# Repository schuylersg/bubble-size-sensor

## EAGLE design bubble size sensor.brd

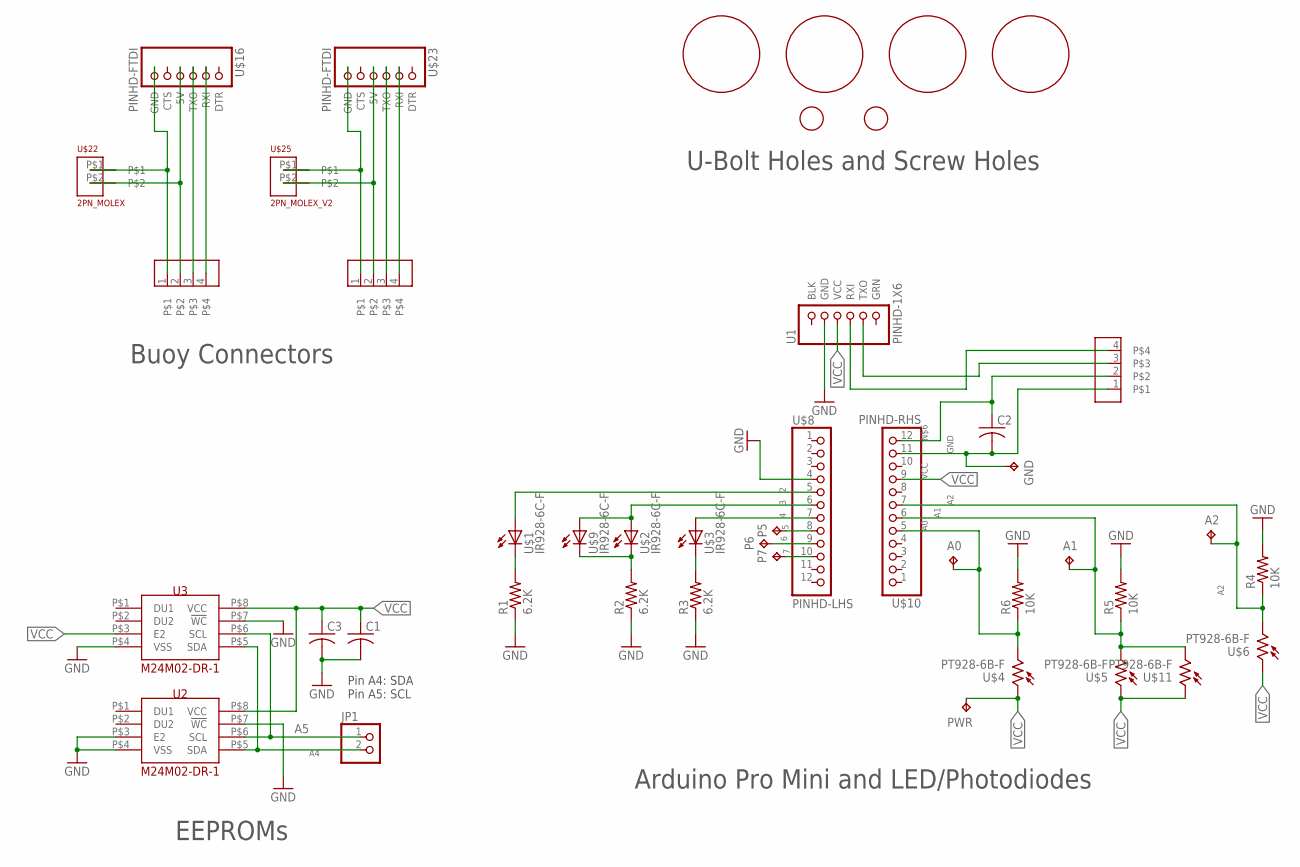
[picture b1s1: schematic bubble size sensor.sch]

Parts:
A0, A1, A2: TPPAD1-13; P1-13
C1, C3: C-USC0603; C0603
C2: C-USC1210; C1210
GND: TPPAD1-13; P1-13
H$13, H$15: M2_SCREW_HOLE
H$17, H$18, H$19, H$20: UBOLT_HOLE
JP1: PINHD-1X2; 1X02
P5, P6, P7: TPPAD1-13; P1-13
PWR: TPPAD1-13; P1-13
R1, R2, R3: 6.2K; R0603
R4, R5, R6: 10K; R0603
U1: PINHD-1X6; 1X6
U2, U3: M24M02-DR-1; SO8N
U$1, U$2, U$3, U$9: IR928-6C-F; LED_LAYOUT
U$4, U$5, U$6, U$11: PT928-6B-F; LED_LAYOUT
U$8: PINHD-LHS; 1X12
U$10: PINHD-RHS; 1X12
U$14, U$21, U$24: MICROFIT3.0_4POS_SMD; MICRO_FIT3.0_4POS-SM
U$16, U$23: PINHD-FTDI; 1X6
U$22: 2PN_MOLEX
U$25: 2PN_MOLEX_V2

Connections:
2: U$1.PWR, U$8.5 (2)
3: U$2.PWR, U$8.6 (3), U$9.PWR
4: U$3.PWR, U$8.7 (4)
5: P5.TP, U$8.8 (5)
6: P6.TP, U$8.9 (6)
7: P7.TP, U$8.10 (7)
A0: A0.TP, R6.1, U$4.RSTR, U$10.5 (A3)
A1: A1.TP, R5.1, U$5.RSTR, U$10.6 (A2), U$11.RSTR
A2: A2.TP, R4.1, U$6.RSTR, U$10.7 (A1)
A4: JP1.2, U2.P$5 (SDA), U3.P$5 (SDA)
A5: JP1.1, U2.P$6 (SCL), U3.P$6 (SCL)
GND: C1.2, C2.2, C3.2, GND.TP, R1.1, R2.1, R3.1, R4.2, R5.2, R6.2, U1.2 (GND), U2.P$3 (E2), U2.P$4 (VSS), U2.P$7 (!WC), U3.P$4 (VSS), U3.P$7 (!WC), U$8.4 (GND), U$10.11, U$14.1
GND2: U$16.6 (GND), U$21.1, U$22.P$1
GND3: U$23.6 (GND), U$24.1, U$25.P$1
unnamed: R1.2, U$1.RSTR
unnamed: R2.2, U$2.RSTR, U$9.RSTR
unnamed: R3.2, U$3.RSTR
unnamed: U$23.4 (5V), U$24.2, U$25.P$2
unnamed: U1.4 (RXI), U$14.4
unnamed: C2.1, U$10.12 (10), U$14.2
unnamed: U1.5 (TXO), U$14.3
unnamed: U$16.4 (5V), U$21.2, U$22.P$2
unnamed: U$16.2 (RXI), U$21.4
unnamed: U$16.3 (TXO), U$21.3
unnamed: U$23.2 (RXI), U$24.4
unnamed: U$23.3 (TXO), U$24.3
VCC: C1.1, C3.1, PWR.TP, U1.3 (VCC), U2.P$8 (VCC), U3.P$3 (E2), U3.P$8 (VCC), U$4.PWR, U$5.PWR, U$6.PWR, U$10.9 (13), U$11.PWR

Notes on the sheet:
Pin A4: SDA Pin A5: SCL
Buoy Connectors
Arduino Pro Mini and LED/Photodiodes
U-Bolt Holes and Screw Holes
EEPROMs

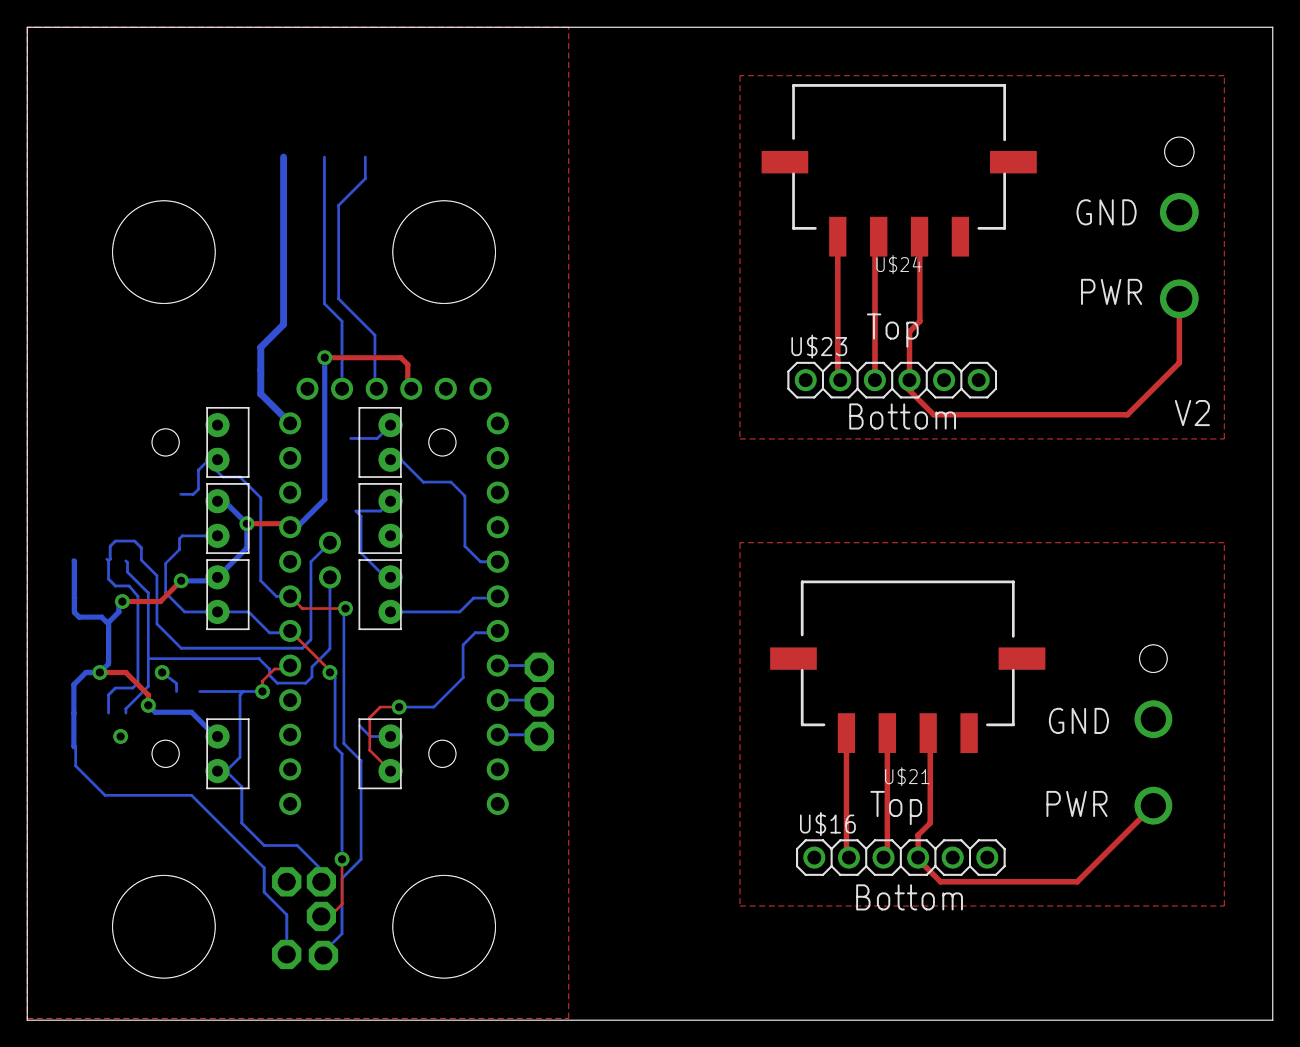
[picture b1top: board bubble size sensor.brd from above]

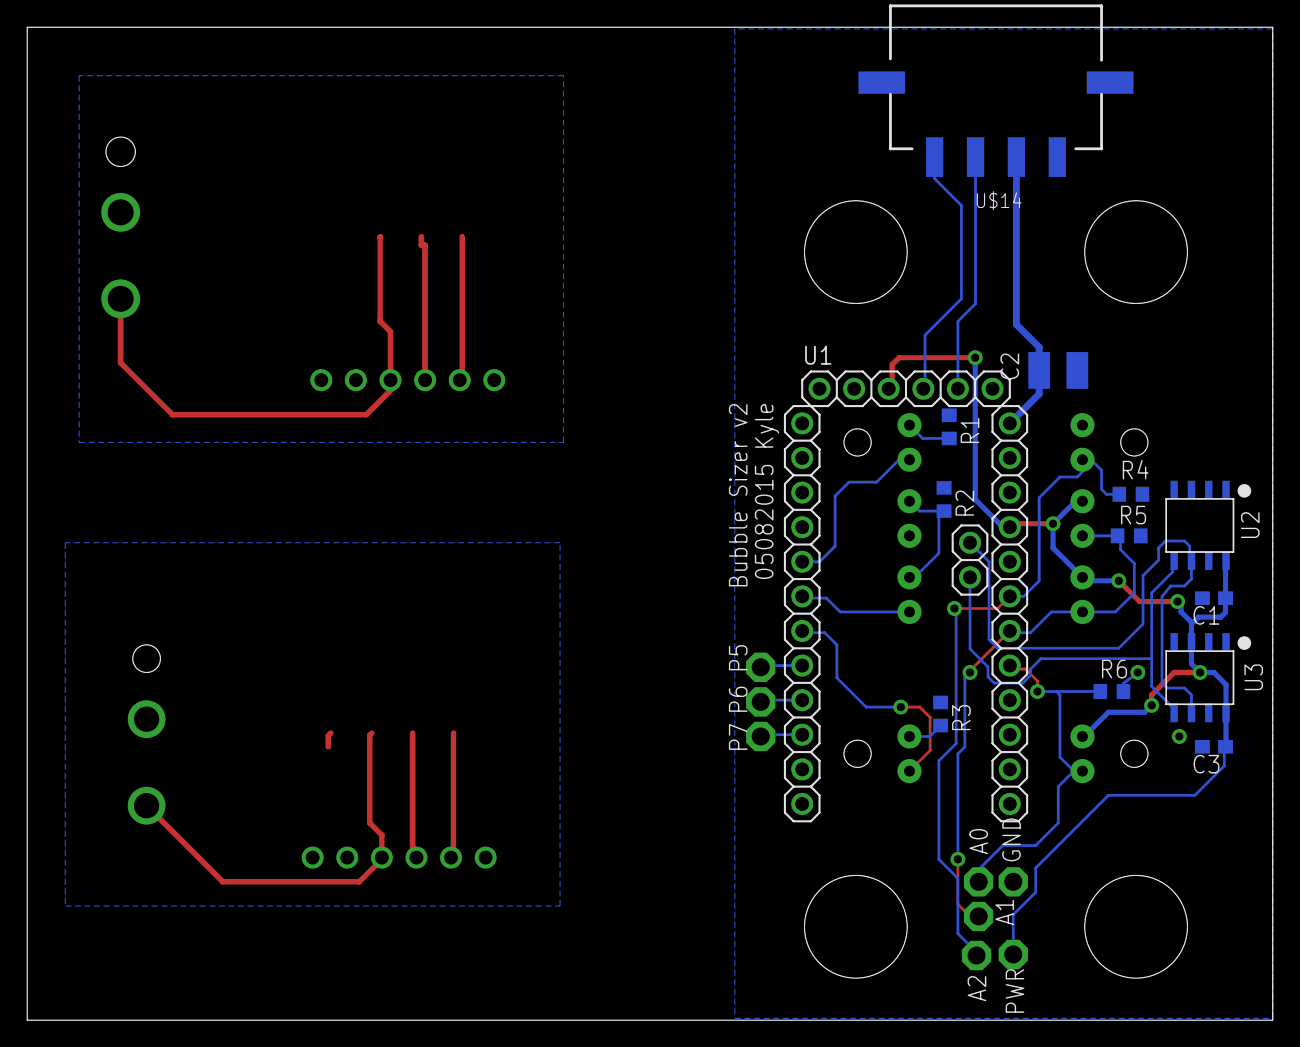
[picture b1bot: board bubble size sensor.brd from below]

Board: 2 copper layers, 91.4 x 72.9 mm, 46 parts (16 on the bottom side), 27 nets.

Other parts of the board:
H$12: M2_SCREW_HOLE
U$7: M2_SCREW_HOLE

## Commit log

2015-05-18 :lollipop: Added .gitattributes & .gitignore files
2015-05-18 Finalized version 6
    Version to include adapters for connecting to buoys.
2015-05-19 Schematic updated with new EEPROMs
    Board layout still in progress.
2015-05-20 Board layout finished
2015-05-20 Added gitignore file.

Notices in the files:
parts and their libraries:
SparkFun-Aesthetics: Licensing: Creative Commons ShareAlike 4.0 International - https://creativecommons.org/licenses/by-sa/4.0
